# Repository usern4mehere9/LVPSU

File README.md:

# LVPSU
Low Voltage Power Supply Unit of Formula Student team "Black Hornets" from the University of Novi Sad Faculty of Technical Sciences

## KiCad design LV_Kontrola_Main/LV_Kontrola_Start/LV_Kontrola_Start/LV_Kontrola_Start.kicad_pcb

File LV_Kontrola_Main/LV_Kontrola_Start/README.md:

# LV\_Kontrola\_Start

Low Voltage Power Supply Unit of Formula Student team "Black Hornets" from the University of Novi Sad Faculty of Technical Sciences

LV\_Kontrola\_Start connectors:

START\_PWR:

1	\[GND]	GND\_START

2	\[GND]	GND\_START

3	\[GND]	GND\_START

4	\[GND]	GND\_START

5	\[VCC]	VCC\_START

6	\[VCC]	VCC\_START

7	\[VCC]	VCC\_START

8	\[VCC]	VCC\_START

COM:

1	\[GND]	GND\_START

2	\[COM]	RS485-B

3	\[GND]	GND\_START

4	\[COM]	RS485-A

START\_OUT\_A:

1	\[VCC]	5V4\_ISO\_1

2	\[GND]	GND\_ISO\_1

3	\[VCC]	5V4\_ISO\_2

4	\[GND]	GND\_ISO\_2

5	\[VCC]	5V4\_ISO\_3

6	\[GND]	GND\_ISO\_3

7	\[VCC]	5V4\_ISO\_4

8	\[GND]	GND\_ISO\_4

9	\[VCC]	3V7\_ISO\_1

10	\[GND]	GND\_ISO\_1

11	\[VCC]	3V7\_ISO\_2

12	\[GND]	GND\_ISO\_2

13	\[VCC]	3V7\_ISO\_3

14	\[GND]	GND\_ISO\_3

15	\[VCC]	3V7\_ISO\_4

16	\[GND]	GND\_ISO\_4

START\_OUT\_B:

1	\[VCC]	5V4\_ISO\_8

2	\[GND]	GND\_ISO\_8

3	\[VCC]	5V4\_ISO\_7

4	\[GND]	GND\_ISO\_7

5	\[VCC]	5V4\_ISO\_6

6	\[GND]	GND\_ISO\_6

7	\[VCC]	5V4\_ISO\_5

8	\[GND]	GND\_ISO\_5

9	\[VCC]	3V7\_ISO\_8

10	\[GND]	GND\_ISO\_8

11	\[VCC]	3V7\_ISO\_7

12	\[GND]	GND\_ISO\_7

13	\[VCC]	3V7\_ISO\_6

14	\[GND]	GND\_ISO\_6

15	\[VCC]	3V7\_ISO\_5

16	\[GND]	GND\_ISO\_5

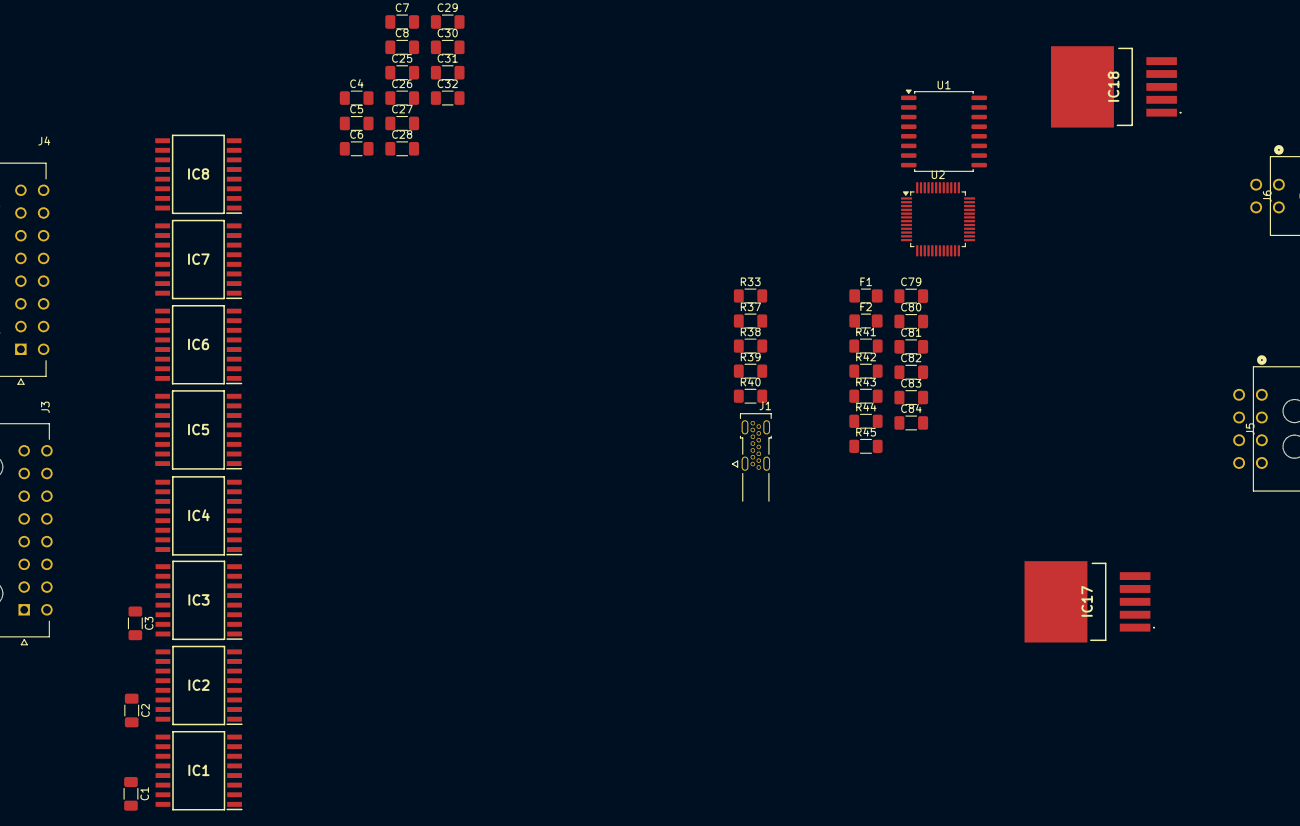
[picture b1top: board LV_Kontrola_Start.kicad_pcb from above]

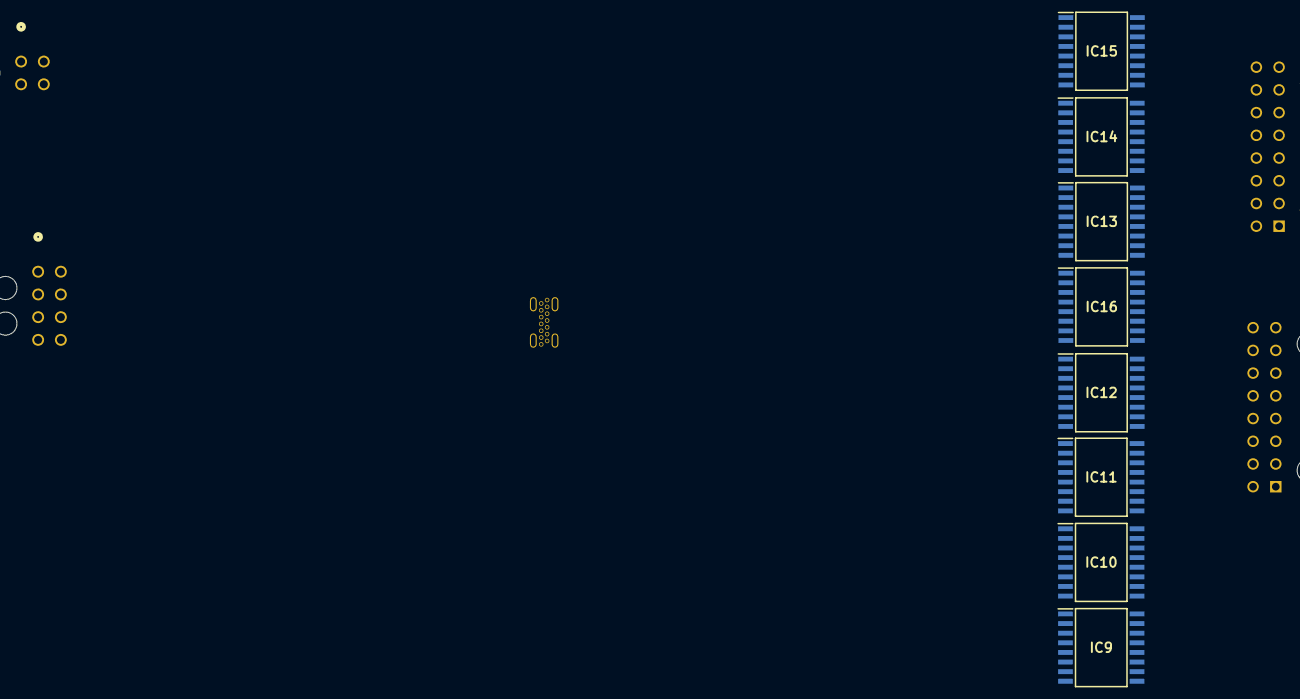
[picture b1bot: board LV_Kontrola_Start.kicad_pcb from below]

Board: 2 copper layers, 59 parts (8 on the bottom side), 44 nets, no tracks yet.

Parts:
C1, C2, C3, C4, C29, C30, C31, C32: 0.1uF; C_1206_3216Metric_Pad1.33x1.80mm_HandSolder
C5, C6, C7, C8, C25, C26, C27, C28, C81, C84: 10uF; C_1206_3216Metric_Pad1.33x1.80mm_HandSolder
C79, C82: 47uF; C_1206_3216Metric_Pad1.33x1.80mm_HandSolder
C80, C83: 22uF; C_1206_3216Metric_Pad1.33x1.80mm_HandSolder
F1, F2: 1A; Fuse_1206_3216Metric_Pad1.42x1.75mm_HandSolder
IC1, IC2, IC3, IC4, IC5, IC6, IC7, IC8, IC9, IC10, IC11, IC12, IC13, IC14, IC15, IC16: UCC12040DVE; SOIC127P1030X265-16N
IC17, IC18: MIC29152WU
J1: 2169890001; MOLEX_2169890001
J3, J4: 430451600; MOLEX_430451600
J5: 430450800; CONN_SD-43045-001_08_MOL
J6: 430450400; CONN_SD-43045-001_04_MOL
R33, R40: 5K1; R_1206_3216Metric_Pad1.30x1.75mm_HandSolder
R37, R38: 27R; R_1206_3216Metric_Pad1.30x1.75mm_HandSolder
R39: 1K5; R_1206_3216Metric_Pad1.30x1.75mm_HandSolder
R41: 34k; R_1206_3216Metric_Pad1.30x1.75mm_HandSolder
R42, R43: 10K; R_1206_3216Metric_Pad1.30x1.75mm_HandSolder
R44: 33k; R_1206_3216Metric_Pad1.30x1.75mm_HandSolder
R45: 10k; R_1206_3216Metric_Pad1.30x1.75mm_HandSolder
U1: ADM2483xRW; SOIC-16W_7.5x10.3mm_P1.27mm
U2: STM32F103C8Tx; LQFP-48_7x7mm_P0.5mm

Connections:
+3V7_ISO1: IC9.14 (VISO), J3.9
+3V7_ISO2: IC10.14 (VISO), J3.11
+3V7_ISO3: IC11.14 (VISO), J3.13
+3V7_ISO4: IC12.14 (VISO), J3.15
+3V7_ISO5: IC15.14 (VISO), J4.15
+3V7_ISO6: IC14.14 (VISO), J4.13
+3V7_ISO7: IC13.14 (VISO), J4.11
+3V7_ISO8: IC16.14 (VISO), J4.9
+5V4_ISO1: C1.1, C5.1, IC1.14 (VISO), J3.1
+5V4_ISO2: C2.1, C6.1, IC2.14 (VISO), J3.3
+5V4_ISO3: C3.1, C7.1, IC3.14 (VISO), J3.5
+5V4_ISO4: C4.1, C8.1, IC4.14 (VISO), J3.7
+5V4_ISO5: C28.1, C32.1, IC8.14 (VISO), J4.7
+5V4_ISO6: C27.1, C31.1, IC7.14 (VISO), J4.5
+5V4_ISO7: C26.1, C30.1, IC6.14 (VISO), J4.3
+5V4_ISO8: C25.1, C29.1, IC5.14 (VISO), J4.1
+5V_START: C82.2, F2.2, IC1.3 (VINP), IC2.3 (VINP), IC3.3 (VINP), IC4.3 (VINP), IC5.3 (VINP), IC6.3 (VINP), IC7.3 (VINP), IC8.3 (VINP), IC9.3 (VINP), IC10.3 (VINP), IC11.3 (VINP), IC12.3 (VINP), IC13.3 (VINP), IC14.3 (VINP), IC15.3 (VINP), IC16.3 (VINP), U1.16 (VDD2)
+V_START: C81.2, C84.2, IC17.2 (IN), IC18.2 (IN), J5.5, J5.6, J5.7, J5.8
CON_DN: J1.A7 (DA-), J1.B7 (DB-), R37.1
CON_DP: J1.A6 (DA+), J1.B6 (DB+), R38.2, R39.2
GND_ISO1: C1.2, C5.2, IC1.9 (GNDS_1), IC1.10 (NC_4), IC1.11 (NC_5), IC1.12 (NC_6), IC1.15 (GNDS_2), IC1.16 (GNDS_3), IC9.9 (GNDS_1), IC9.10 (NC_4), IC9.11 (NC_5), IC9.12 (NC_6), IC9.15 (GNDS_2), IC9.16 (GNDS_3), J3.2, J3.10
GND_ISO2: C2.2, C6.2, IC2.9 (GNDS_1), IC2.10 (NC_4), IC2.11 (NC_5), IC2.12 (NC_6), IC2.15 (GNDS_2), IC2.16 (GNDS_3), IC10.9 (GNDS_1), IC10.10 (NC_4), IC10.11 (NC_5), IC10.12 (NC_6), IC10.15 (GNDS_2), IC10.16 (GNDS_3), J3.4, J3.12
GND_ISO3: C3.2, C7.2, IC3.9 (GNDS_1), IC3.10 (NC_4), IC3.11 (NC_5), IC3.12 (NC_6), IC3.15 (GNDS_2), IC3.16 (GNDS_3), IC11.9 (GNDS_1), IC11.10 (NC_4), IC11.11 (NC_5), IC11.12 (NC_6), IC11.15 (GNDS_2), IC11.16 (GNDS_3), J3.6, J3.14
GND_ISO4: C4.2, C8.2, IC4.9 (GNDS_1), IC4.10 (NC_4), IC4.11 (NC_5), IC4.12 (NC_6), IC4.15 (GNDS_2), IC4.16 (GNDS_3), IC12.9 (GNDS_1), IC12.10 (NC_4), IC12.11 (NC_5), IC12.12 (NC_6), IC12.15 (GNDS_2), IC12.16 (GNDS_3), J3.8, J3.16
GND_ISO5: C28.2, C32.2, IC8.9 (GNDS_1), IC8.10 (NC_4), IC8.11 (NC_5), IC8.12 (NC_6), IC8.15 (GNDS_2), IC8.16 (GNDS_3), IC15.9 (GNDS_1), IC15.10 (NC_4), IC15.11 (NC_5), IC15.12 (NC_6), IC15.15 (GNDS_2), IC15.16 (GNDS_3), J4.8, J4.16
GND_ISO6: C27.2, C31.2, IC7.9 (GNDS_1), IC7.10 (NC_4), IC7.11 (NC_5), IC7.12 (NC_6), IC7.15 (GNDS_2), IC7.16 (GNDS_3), IC14.9 (GNDS_1), IC14.10 (NC_4), IC14.11 (NC_5), IC14.12 (NC_6), IC14.15 (GNDS_2), IC14.16 (GNDS_3), J4.6, J4.14
GND_ISO7: C26.2, C30.2, IC6.9 (GNDS_1), IC6.10 (NC_4), IC6.11 (NC_5), IC6.12 (NC_6), IC6.15 (GNDS_2), IC6.16 (GNDS_3), IC13.9 (GNDS_1), IC13.10 (NC_4), IC13.11 (NC_5), IC13.12 (NC_6), IC13.15 (GNDS_2), IC13.16 (GNDS_3), J4.4, J4.12
GND_ISO8: C25.2, C29.2, IC5.9 (GNDS_1), IC5.10 (NC_4), IC5.11 (NC_5), IC5.12 (NC_6), IC5.15 (GNDS_2), IC5.16 (GNDS_3), IC16.9 (GNDS_1), IC16.10 (NC_4), IC16.11 (NC_5), IC16.12 (NC_6), IC16.15 (GNDS_2), IC16.16 (GNDS_3), J4.2, J4.10
unnamed: IC17.5 (ADJ), R41.1, R42.2
unnamed: C80.2, F1.1, IC17.4 (OUT)
unnamed: IC18.5 (ADJ), R44.1, R45.2
unnamed: C83.2, F2.1, IC18.4 (OUT)
unnamed: J1.A5 (CC1), R33.1
unnamed: J1.B5 (CC2), R40.2
unnamed: R42.1, R43.2
RESET: C79.1, C80.1, C81.1, C82.1, C83.1, C84.1, IC1.2 (GNDP), IC1.4 (SYNC), IC1.6 (NC_1), IC1.7 (NC_2), IC1.8 (NC_3), IC2.2 (GNDP), IC2.4 (SYNC), IC2.6 (NC_1), IC2.7 (NC_2), IC2.8 (NC_3), IC3.2 (GNDP), IC3.4 (SYNC), IC3.6 (NC_1), IC3.7 (NC_2), IC3.8 (NC_3), IC4.2 (GNDP), IC4.4 (SYNC), IC4.6 (NC_1), IC4.7 (NC_2), IC4.8 (NC_3), IC5.2 (GNDP), IC5.4 (SYNC), IC5.6 (NC_1), IC5.7 (NC_2), IC5.8 (NC_3), IC6.2 (GNDP), IC6.4 (SYNC), IC6.6 (NC_1), IC6.7 (NC_2), IC6.8 (NC_3), IC7.2 (GNDP), IC7.4 (SYNC), IC7.6 (NC_1), IC7.7 (NC_2), IC7.8 (NC_3), IC8.2 (GNDP), IC8.4 (SYNC), IC8.6 (NC_1), IC8.7 (NC_2), IC8.8 (NC_3), IC9.2 (GNDP), IC9.4 (SYNC), IC9.6 (NC_1), IC9.7 (NC_2), IC9.8 (NC_3), IC10.2 (GNDP), IC10.4 (SYNC), IC10.6 (NC_1), IC10.7 (NC_2), IC10.8 (NC_3), IC11.2 (GNDP), IC11.4 (SYNC), IC11.6 (NC_1), IC11.7 (NC_2), IC11.8 (NC_3), IC12.2 (GNDP), IC12.4 (SYNC), IC12.6 (NC_1), IC12.7 (NC_2), IC12.8 (NC_3), IC13.2 (GNDP), IC13.4 (SYNC), IC13.6 (NC_1), IC13.7 (NC_2), IC13.8 (NC_3), IC14.2 (GNDP), IC14.4 (SYNC), IC14.6 (NC_1), IC14.7 (NC_2), IC14.8 (NC_3), IC15.2 (GNDP), IC15.4 (SYNC), IC15.6 (NC_1), IC15.7 (NC_2), IC15.8 (NC_3), IC16.2 (GNDP), IC16.4 (SYNC), IC16.6 (NC_1), IC16.7 (NC_2), IC16.8 (NC_3), IC17.3 (GND_1), IC17.6 (GND_2), IC18.3 (GND_1), IC18.6 (GND_2), J1.A1 (GND1), J1.A12 (GND2), J1.B1 (GND3), J1.B12 (GND4), J1.SH1 (SHIELD1), J1.SH2 (SHIELD2), J1.SH3 (SHIELD3), J1.SH4 (SHIELD4), J5.1, J5.2, J5.3, J5.4, J6.1, J6.3, R33.2, R40.1, R43.1, R45.1, U1.2 (GND1), U1.8 (GND1), U1.9 (GND2), U1.15 (GND2), U2.7 (NRST), U2.8 (VSSA), U2.23 (VSS), U2.35 (VSS), U2.47 (VSS)
RS485-A: J6.4, U1.12 (A)
RS485-B: J6.2, U1.13 (B)
RS485-DIR: U1.4 (~RE), U1.5 (DE), U2.2 (PC13)
RS485-RX: U1.3 (RxD), U2.43 (PB7)
RS485-TX: U1.6 (TxD), U2.42 (PB6)
USB_DM: R37.2, U2.32 (PA11)
USB_DP: R38.1, U2.33 (PA12)
VBAT: C79.2, F1.2, R39.1, U1.1 (VDD1), U1.7 (PV), U2.1 (VBAT), U2.9 (VDDA), U2.24 (VDD), U2.36 (VDD), U2.48 (VDD)

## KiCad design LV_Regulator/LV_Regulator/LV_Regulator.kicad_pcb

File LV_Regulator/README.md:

# LV\_Regulator

Low Voltage Power Supply Unit of Formula Student team "Black Hornets" from the University of Novi Sad Faculty of Technical Sciences

LV\_Regulator connectors:

PWR\_IN:

1	\[GND]	BAT-

2	\[GND]	BAT-

3	\[GND]	BAT-

4	\[GND]	BAT-

5	\[VCC]	BAT+

6	\[VCC]	BAT+

7	\[VCC]	BAT+

8	\[VCC]	BAT+

COM:

1	\[COM]	RS485-B

2	\[COM]	RS485-A

3	\[GND]	GND\_ISO

4	\[VCC]	+5V\_ISO

START:

1	\[GND]	GND

2	\[GND]	GND

3	\[VCC]	5V\_EXT

4	\[VCC]	3V3\_EXT

PWR\_OUT:

1	\[VCC]	VOUT

2	\[VCC]	VOUT

3	\[VCC]	VOUT

4	\[VCC]	VOUT

5	\[GND]	GND

6	\[GND]	GND

7	\[GND]	GND

8	\[GND]	GND

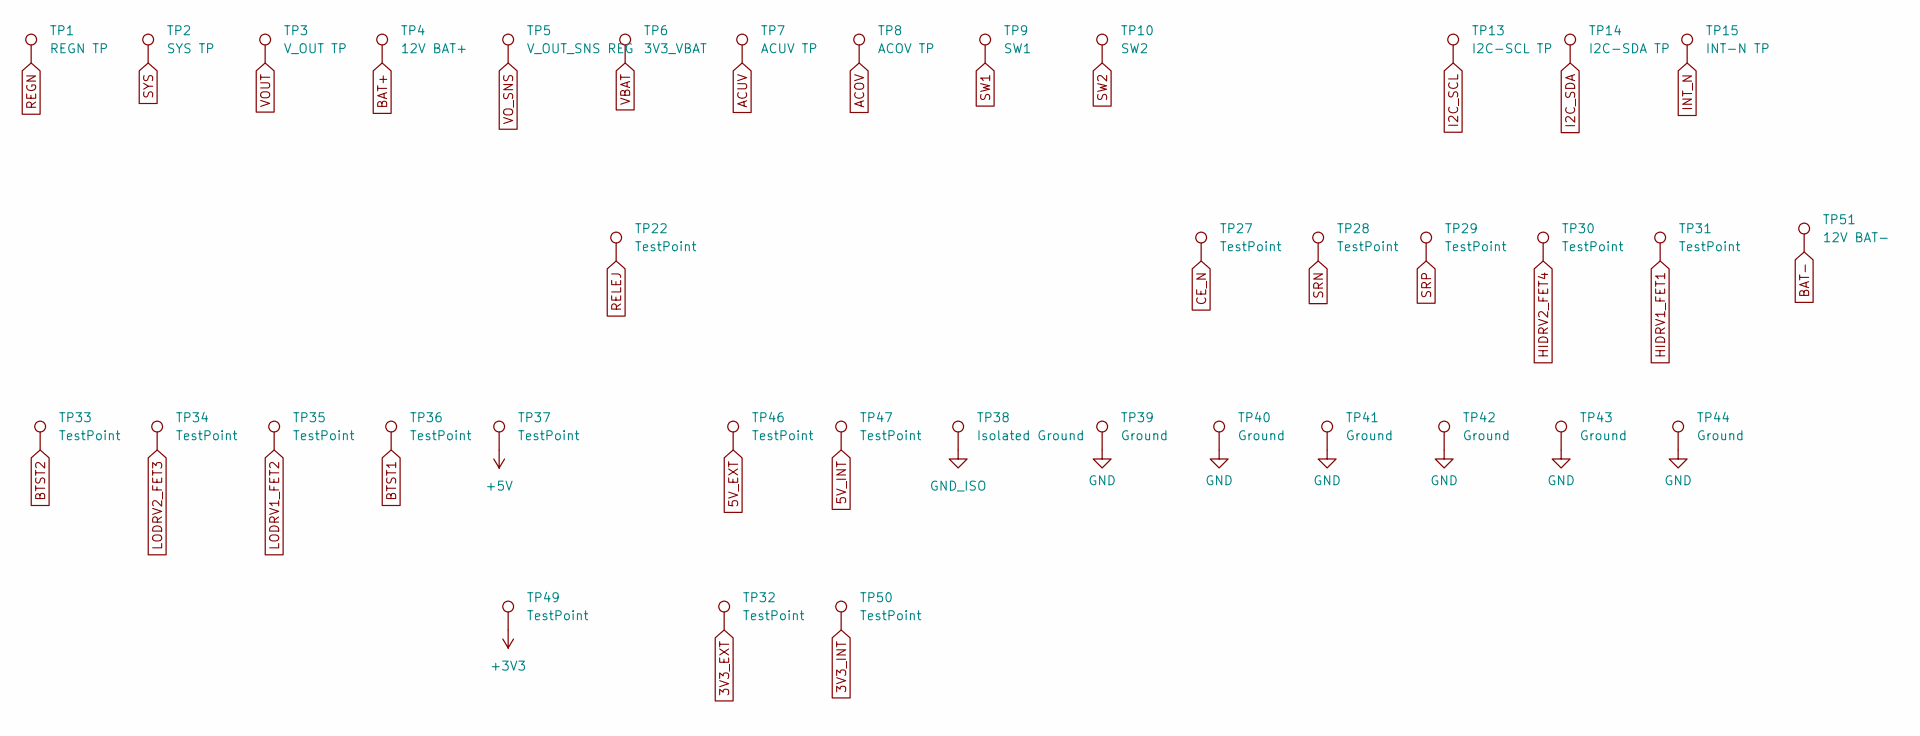
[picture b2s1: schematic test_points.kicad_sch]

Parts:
TP1: REGN TP; TestPoint_Pad_1.0x1.0mm
TP2: SYS TP; TestPoint_Pad_1.0x1.0mm
TP3: V_OUT TP; TestPoint_Pad_1.0x1.0mm
TP4: 12V BAT+; TestPoint_Pad_1.0x1.0mm
TP5: V_OUT_SNS REG; TestPoint_Pad_1.0x1.0mm
TP6: 3V3_VBAT; TestPoint_Pad_1.0x1.0mm
TP7: ACUV TP; TestPoint_Pad_1.0x1.0mm
TP8: ACOV TP; TestPoint_Pad_1.0x1.0mm
TP9: SW1; TestPoint_Pad_1.0x1.0mm
TP10: SW2; TestPoint_Pad_1.0x1.0mm
TP13: I2C-SCL TP; TestPoint_Pad_1.0x1.0mm
TP14: I2C-SDA TP; TestPoint_Pad_1.0x1.0mm
TP15: INT-N TP; TestPoint_Pad_1.0x1.0mm
TP22, TP27, TP28, TP29, TP30, TP31, TP32, TP33, TP34, TP35, TP36, TP37, TP46, TP47, TP49, TP50: TestPoint; TestPoint_Pad_1.0x1.0mm
TP38: Isolated Ground; TestPoint_Pad_1.0x1.0mm
TP39, TP40, TP41, TP42, TP43, TP44: Ground; TestPoint_Pad_1.0x1.0mm
TP51: 12V BAT-; TestPoint_Pad_1.0x1.0mm

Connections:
3V3_EXT: TP32.1 (1_1); also elsewhere on the board
3V3_INT: TP50.1 (1_1); also elsewhere on the board
5V_EXT: TP46.1 (1_1); also elsewhere on the board
5V_INT: TP47.1 (1_1); also elsewhere on the board
+5V: TP37.1 (1_1); also elsewhere on the board
ACOV: TP8.1 (1_1); also elsewhere on the board
ACUV: TP7.1 (1_1); also elsewhere on the board
BAT+: TP4.1 (1_1); also elsewhere on the board
BAT-: TP51.1 (1_1); also elsewhere on the board
BTST1: TP36.1 (1_1); also elsewhere on the board
BTST2: TP33.1 (1_1); also elsewhere on the board
CE_N: TP27.1 (1_1); also elsewhere on the board
GND: TP39.1 (1_1), TP40.1 (1_1), TP41.1 (1_1), TP42.1 (1_1), TP43.1 (1_1), TP44.1 (1_1); also elsewhere on the board
GND_ISO: TP38.1 (1_1); also elsewhere on the board
HIDRV1_FET1: TP31.1 (1_1); also elsewhere on the board
HIDRV2_FET4: TP30.1 (1_1); also elsewhere on the board
I2C_SCL: TP13.1 (1_1); also elsewhere on the board
I2C_SDA: TP14.1 (1_1); also elsewhere on the board
INT_N: TP15.1 (1_1); also elsewhere on the board
LODRV1_FET2: TP35.1 (1_1); also elsewhere on the board
LODRV2_FET3: TP34.1 (1_1); also elsewhere on the board
REGN: TP1.1 (1_1); also elsewhere on the board
RELEJ: TP22.1 (1_1); also elsewhere on the board
SRN: TP28.1 (1_1); also elsewhere on the board
SRP: TP29.1 (1_1); also elsewhere on the board
SW1: TP9.1 (1_1); also elsewhere on the board
SW2: TP10.1 (1_1); also elsewhere on the board
SYS: TP2.1 (1_1); also elsewhere on the board
VBAT: TP6.1 (1_1), TP49.1 (1_1); also elsewhere on the board
VOUT: TP3.1 (1_1), TP5.1 (1_1); also elsewhere on the board

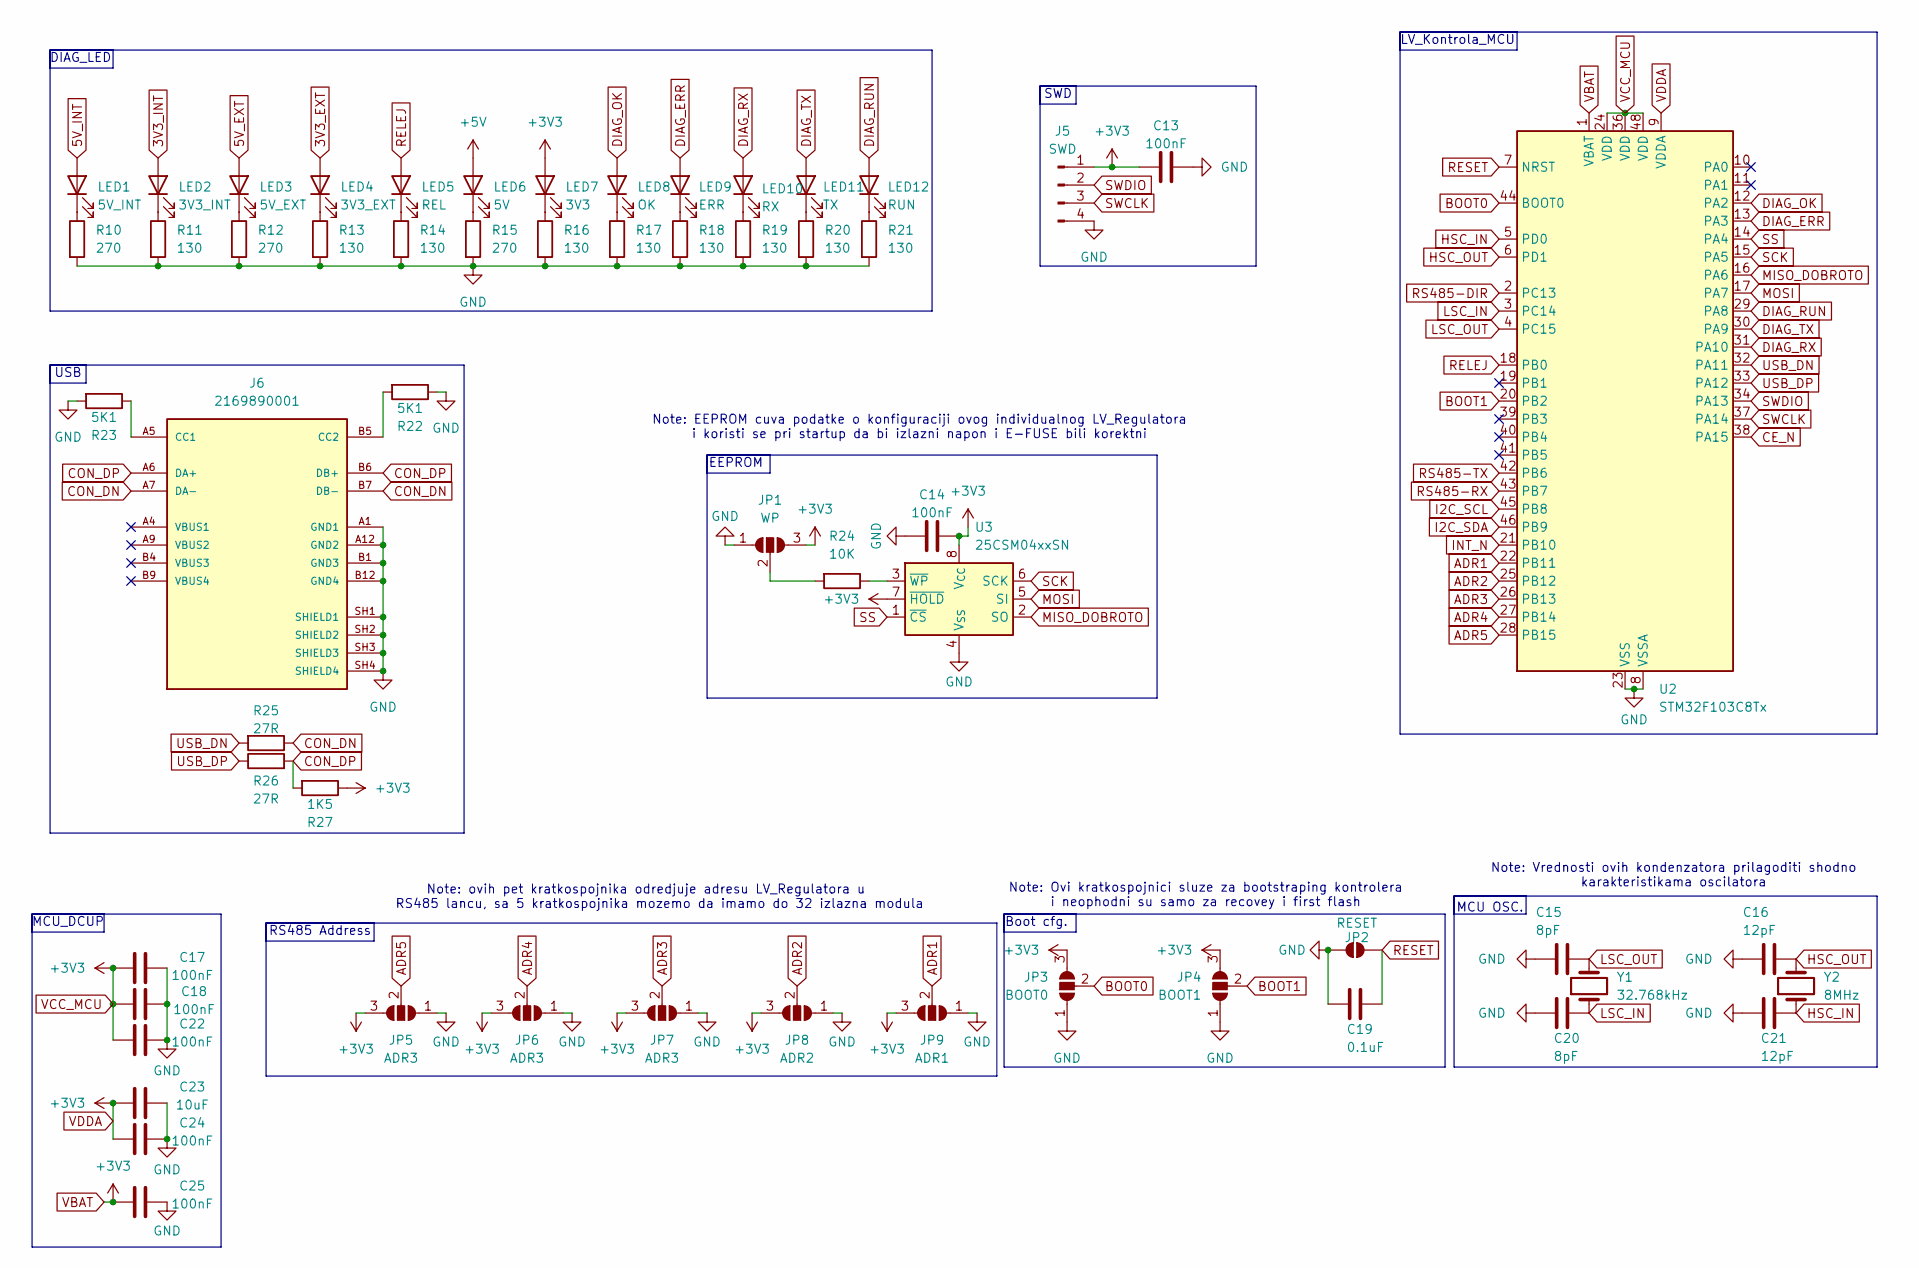
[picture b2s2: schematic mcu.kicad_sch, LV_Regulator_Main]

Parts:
C13, C14, C17, C18, C22, C24, C25: 100nF; C_1206_3216Metric_Pad1.33x1.80mm_HandSolder
C15, C20: 8pF; C_1206_3216Metric_Pad1.33x1.80mm_HandSolder
C16, C21: 12pF; C_1206_3216Metric_Pad1.33x1.80mm_HandSolder
C19: 0.1uF; C_1206_3216Metric_Pad1.33x1.80mm_HandSolder
C23: 10uF; C_1206_3216Metric_Pad1.33x1.80mm_HandSolder
J5: SWD; PinHeader_1x04_P2.54mm_Vertical
J6: 2169890001; MOLEX_2169890001; PARTREV B
JP1: WP; SolderJumper-3_P1.3mm_Open_RoundedPad1.0x1.5mm
JP2: RESET; SolderJumper-2_P1.3mm_Open_RoundedPad1.0x1.5mm
JP3: BOOT0; SolderJumper-3_P1.3mm_Open_RoundedPad1.0x1.5mm
JP4: BOOT1; SolderJumper-3_P1.3mm_Open_RoundedPad1.0x1.5mm
JP5, JP6, JP7: ADR3; SolderJumper-3_P1.3mm_Open_RoundedPad1.0x1.5mm
JP8: ADR2; SolderJumper-3_P1.3mm_Open_RoundedPad1.0x1.5mm
JP9: ADR1; SolderJumper-3_P1.3mm_Open_RoundedPad1.0x1.5mm
LED1: 5V_INT; LED_1206_3216Metric_Pad1.42x1.75mm_HandSolder
LED2: 3V3_INT; LED_1206_3216Metric_Pad1.42x1.75mm_HandSolder
LED3: 5V_EXT; LED_1206_3216Metric_Pad1.42x1.75mm_HandSolder
LED4: 3V3_EXT; LED_1206_3216Metric_Pad1.42x1.75mm_HandSolder
LED5: REL; LED_1206_3216Metric_Pad1.42x1.75mm_HandSolder
LED6: 5V; LED_1206_3216Metric_Pad1.42x1.75mm_HandSolder
LED7: 3V3; LED_1206_3216Metric_Pad1.42x1.75mm_HandSolder
LED8: OK; LED_1206_3216Metric_Pad1.42x1.75mm_HandSolder
LED9: ERR; LED_1206_3216Metric_Pad1.42x1.75mm_HandSolder
LED10: RX; LED_1206_3216Metric_Pad1.42x1.75mm_HandSolder
LED11: TX; LED_1206_3216Metric_Pad1.42x1.75mm_HandSolder
LED12: RUN; LED_1206_3216Metric_Pad1.42x1.75mm_HandSolder
R10, R12, R15: 270; R_1206_3216Metric_Pad1.30x1.75mm_HandSolder
R11, R13, R14, R16, R17, R18, R19, R20, R21: 130; R_1206_3216Metric_Pad1.30x1.75mm_HandSolder
R22, R23: 5K1; R_1206_3216Metric_Pad1.30x1.75mm_HandSolder
R24: 10K; R_1206_3216Metric_Pad1.30x1.75mm_HandSolder
R25, R26: 27R; R_1206_3216Metric_Pad1.30x1.75mm_HandSolder
R27: 1K5; R_1206_3216Metric_Pad1.30x1.75mm_HandSolder
U2: STM32F103C8Tx; LQFP-48_7x7mm_P0.5mm
U3: 25CSM04xxSN; SOIC-8_3.9x4.9mm_P1.27mm
Y1: 32.768kHz; Crystal_SMD_EuroQuartz_EQ161-2Pin_3.2x1.5mm_HandSoldering
Y2: 8MHz; Crystal_SMD_5032-2Pin_5.0x3.2mm_HandSoldering

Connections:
3V3_EXT: LED4.2 (A); also elsewhere on the board
3V3_INT: LED2.2 (A); also elsewhere on the board
5V_EXT: LED3.2 (A); also elsewhere on the board
5V_INT: LED1.2 (A); also elsewhere on the board
+5V: LED6.2 (A); also elsewhere on the board
ADR1: JP9.2 (C), U2.22 (PB11)
ADR2: JP8.2 (C), U2.25 (PB12)
ADR3: JP7.2 (C), U2.26 (PB13)
ADR4: JP6.2 (C), U2.27 (PB14)
ADR5: JP5.2 (C), U2.28 (PB15)
BOOT0: JP3.2 (C), U2.44 (BOOT0)
BOOT1: JP4.2 (C), U2.20 (PB2)
CE_N: U2.38 (PA15); also elsewhere on the board
CON_DN: J6.A7 (DA-), J6.B7 (DB-), R25.1
CON_DP: J6.A6 (DA+), J6.B6 (DB+), R26.2, R27.2
DIAG_ERR: LED9.2 (A), U2.13 (PA3)
DIAG_OK: LED8.2 (A), U2.12 (PA2)
DIAG_RUN: LED12.2 (A), U2.29 (PA8)
DIAG_RX: LED10.2 (A), U2.31 (PA10)
DIAG_TX: LED11.2 (A), U2.30 (PA9)
GND: C13.1, C14.2, C15.1, C16.1, C17.2, C18.2, C19.2, C20.2, C21.2, C22.2, C23.2, C24.2, C25.2, J5.4, J6.A1 (GND1), J6.A12 (GND2), J6.B1 (GND3), J6.B12 (GND4), J6.SH1 (SHIELD1), J6.SH2 (SHIELD2), J6.SH3 (SHIELD3), J6.SH4 (SHIELD4), JP1.1 (A), JP2.1 (A), JP3.1 (A), JP4.1 (A), JP5.1 (A), JP6.1 (A), JP7.1 (A), JP8.1 (A), JP9.1 (A), R10.2, R11.2, R12.2, R13.2, R14.2, R15.2, R16.2, R17.2, R18.2, R19.2, R20.2, R21.2, R22.1, R23.2, U2.8 (VSSA), U2.23 (VSS), U2.35 (VSS), U2.47 (VSS), U3.4 (V_{SS}); also elsewhere on the board
HSC_IN: C21.1, U2.5 (PD0), Y2.1
HSC_OUT: C16.2, U2.6 (PD1), Y2.2
I2C_SCL: U2.45 (PB8); also elsewhere on the board
I2C_SDA: U2.46 (PB9); also elsewhere on the board
INT_N: U2.21 (PB10); also elsewhere on the board
LSC_IN: C20.1, U2.3 (PC14), Y1.1
LSC_OUT: C15.2, U2.4 (PC15), Y1.2
MISO_DOBROTO: U2.16 (PA6), U3.2 (SO)
MOSI: U2.17 (PA7), U3.5 (SI)
unnamed: J6.A5 (CC1), R23.1
unnamed: J6.B5 (CC2), R22.2
unnamed: JP1.2 (C), R24.2
unnamed: LED1.1 (K), R10.1
unnamed: LED2.1 (K), R11.1
unnamed: LED3.1 (K), R12.1
unnamed: LED4.1 (K), R13.1
unnamed: LED5.1 (K), R14.1
unnamed: LED6.1 (K), R15.1
unnamed: LED7.1 (K), R16.1
unnamed: LED8.1 (K), R17.1
unnamed: LED9.1 (K), R18.1
unnamed: LED10.1 (K), R19.1
unnamed: LED11.1 (K), R20.1
unnamed: LED12.1 (K), R21.1
unnamed: R24.1, U3.3 (~WP)
RELEJ: LED5.2 (A), U2.18 (PB0); also elsewhere on the board
RESET: C19.1, JP2.2 (B), U2.7 (NRST)
RS485-DIR: U2.2 (PC13); also elsewhere on the board
RS485-RX: U2.43 (PB7); also elsewhere on the board
RS485-TX: U2.42 (PB6); also elsewhere on the board
SCK: U2.15 (PA5), U3.6 (SCK)
SS: U2.14 (PA4), U3.1 (~CS)
SWCLK: J5.3, U2.37 (PA14)
SWDIO: J5.2, U2.34 (PA13)
USB_DN: R25.2, U2.32 (PA11)
USB_DP: R26.1, U2.33 (PA12)
VBAT: C13.2, C14.1, C17.1, C18.1, C22.1, C23.1, C24.1, C25.1, J5.1, JP1.3 (B), JP3.3 (B), JP4.3 (B), JP5.3 (B), JP6.3 (B), JP7.3 (B), JP8.3 (B), JP9.3 (B), LED7.2 (A), R27.1, U2.1 (VBAT), U2.9 (VDDA), U2.24 (VDD), U2.36 (VDD), U2.48 (VDD), U3.7 (~HOLD), U3.8 (V_{CC}); also elsewhere on the board

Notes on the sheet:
RS485 Address
MCU_DCUP
EEPROM
LV_Kontrola_MCU
Note: Ovi kratkospojnici sluze za bootstraping kontrolera i neophodni su samo za recovey i first flash
USB
Boot cfg.
Note: Vrednosti ovih kondenzatora prilagoditi shodno karakteristikama oscilatora
Note: ovih pet kratkospojnika odredjuje adresu LV_Regulatora u RS485 lancu, sa 5 kratkospojnika mozemo da imamo do 32 izlazna modula
Note: EEPROM cuva podatke o konfiguraciji ovog individualnog LV_Regulatora i koristi se pri startup da bi izlazni napon i E-FUSE bili korektni
MCU OSC.
SWD
DIAG_LED

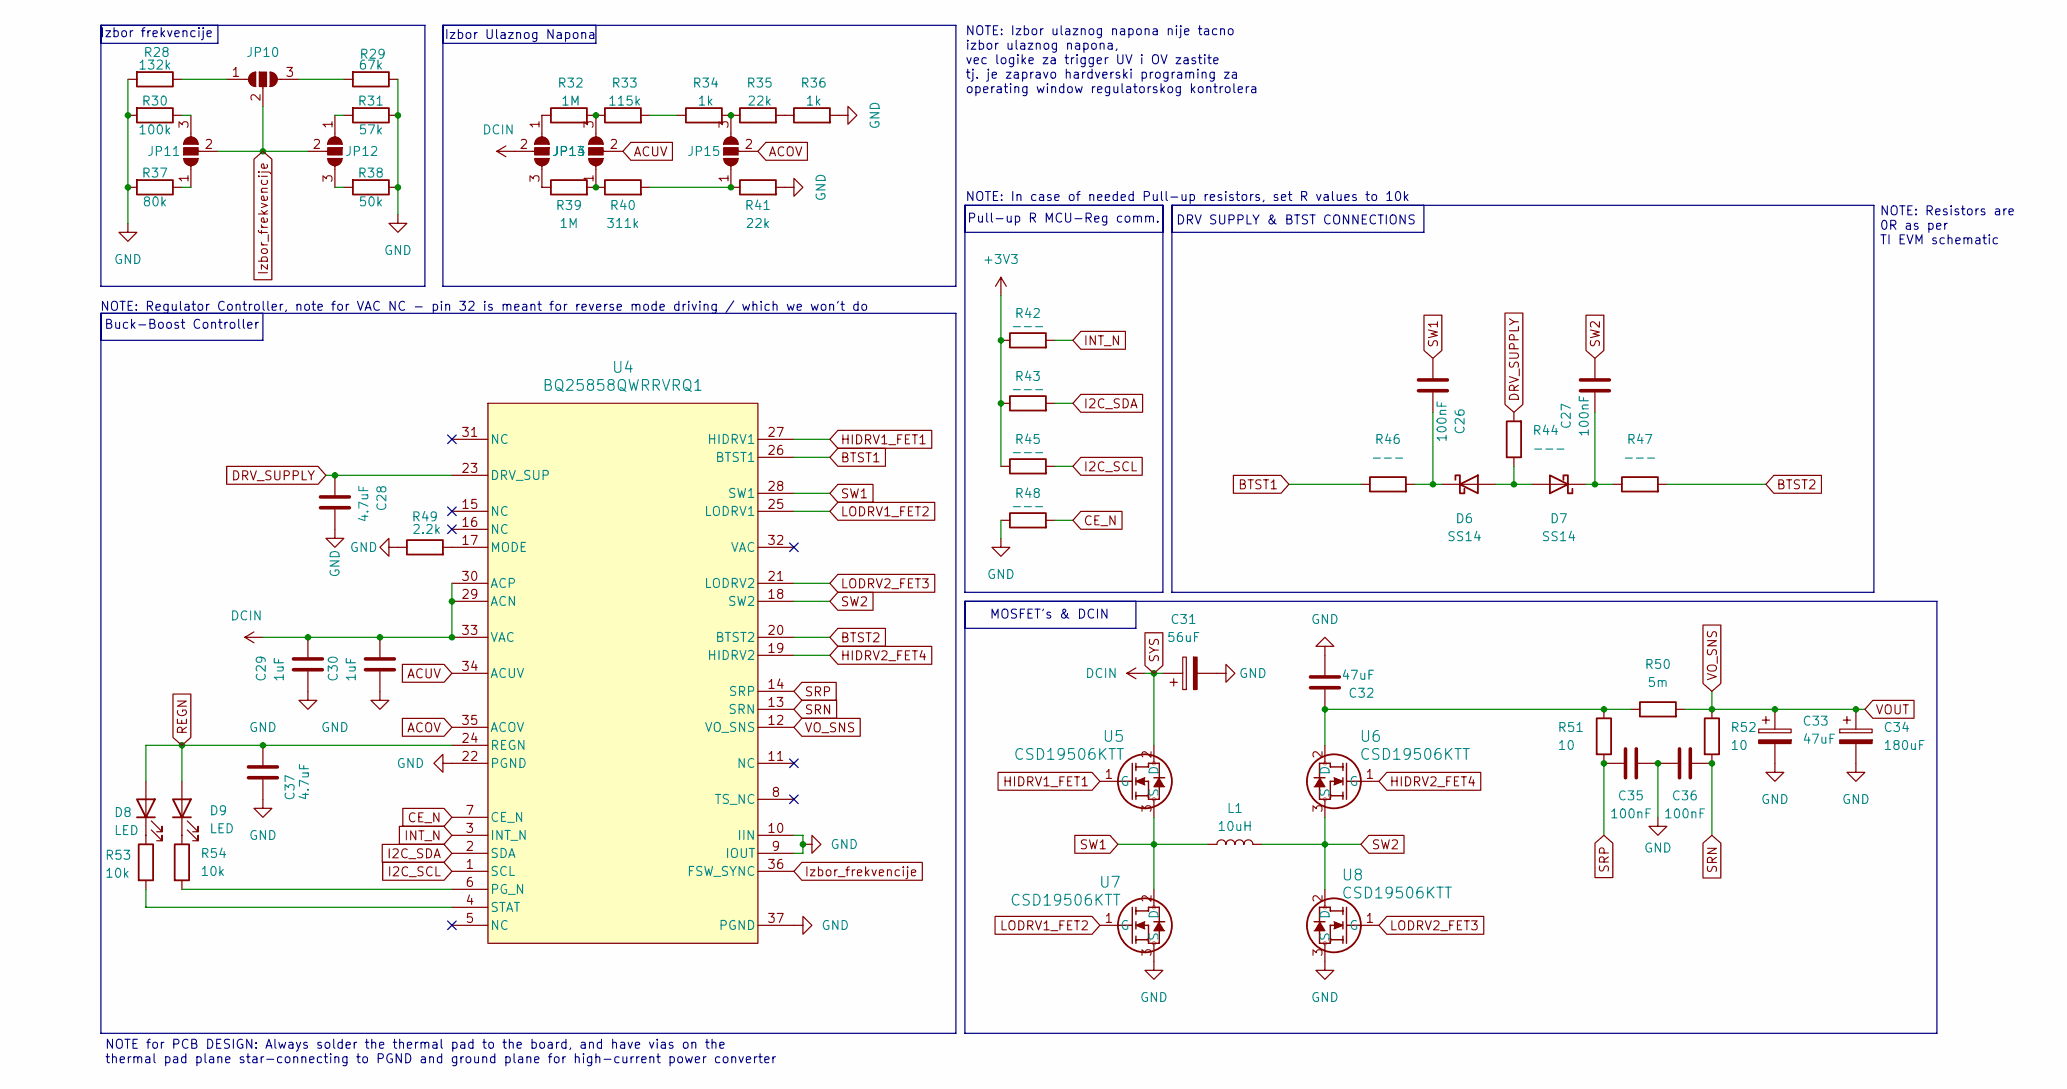
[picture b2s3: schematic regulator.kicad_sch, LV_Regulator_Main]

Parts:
C26, C27, C35, C36: 100nF; C_1206_3216Metric
C28, C37: 4.7uF; C_1206_3216Metric
C29, C30: 1uF; C_1206_3216Metric
C31: 56uF; CP_Elec_10x10
C32, C33: 47uF; CP_Elec_10x10
C34: 180uF; CAP_UCD_12P5X13P5_NCH
D6, D7: SS14; CR_SMA_403AE_OSI
D8, D9: LED; D_1206_3216Metric_Pad1.42x1.75mm_HandSolder
JP10, JP11, JP12, JP13, JP14, JP15: SolderJumper_3_Open; SolderJumper-3_P1.3mm_Open_RoundedPad1.0x1.5mm
L1: 10uH; L_APV_APH1770
R28: 132k; R_1206_3216Metric_Pad1.30x1.75mm_HandSolder
R29: 67k; R_1206_3216Metric_Pad1.30x1.75mm_HandSolder
R30: 100k; R_1206_3216Metric_Pad1.30x1.75mm_HandSolder
R31: 57k; R_1206_3216Metric_Pad1.30x1.75mm_HandSolder
R32, R39: 1M; R_1206_3216Metric_Pad1.30x1.75mm_HandSolder
R33: 115k; R_1206_3216Metric_Pad1.30x1.75mm_HandSolder
R34, R36: 1k; R_1206_3216Metric_Pad1.30x1.75mm_HandSolder
R35, R41: 22k; R_1206_3216Metric_Pad1.30x1.75mm_HandSolder
R37: 80k; R_1206_3216Metric_Pad1.30x1.75mm_HandSolder
R38: 50k; R_1206_3216Metric_Pad1.30x1.75mm_HandSolder
R40: 311k; R_1206_3216Metric_Pad1.30x1.75mm_HandSolder
R42, R43, R44, R45, R46, R47, R48: ---; R_1206_3216Metric_Pad1.30x1.75mm_HandSolder
R49: 2.2k; R_1206_3216Metric_Pad1.30x1.75mm_HandSolder
R50: 5m; RESC50110X70N
R51, R52: 10; R_1206_3216Metric_Pad1.30x1.75mm_HandSolder
R53, R54: 10k; R_1206_3216Metric_Pad1.30x1.75mm_HandSolder
U4: BQ25858QWRRVRQ1; RRV0036B-IPC_A
U5, U6, U7, U8: CSD19506KTT; DDPAK&slash_TO-263_KTT_TEX

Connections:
ACOV: JP15.2 (C), U4.35 (ACOV); also elsewhere on the board
ACUV: JP14.2 (C), U4.34 (ACUV); also elsewhere on the board
BTST1: R46.1, U4.26 (BTST1); also elsewhere on the board
BTST2: R47.2, U4.20 (BTST2); also elsewhere on the board
CE_N: R48.2, U4.7 (CE_N); also elsewhere on the board
DRV_SUPPLY: C28.1, R44.2, U4.23 (DRV_SUP)
GND: C28.2, C29.1, C30.1, C31.2, C32.2, C33.2, C34.2, C35.2, C36.1, C37.1, R28.2, R29.1, R30.2, R31.1, R36.2, R37.2, R38.1, R41.2, R48.1, R49.1, U4.9 (IOUT), U4.10 (IIN), U4.22 (PGND), U4.37 (PGND), U7.3 (S), U8.3 (S); also elsewhere on the board
HIDRV1_FET1: U4.27 (HIDRV1), U5.1 (G); also elsewhere on the board
HIDRV2_FET4: U4.19 (HIDRV2), U6.1 (G); also elsewhere on the board
I2C_SCL: R45.2, U4.1 (SCL); also elsewhere on the board
I2C_SDA: R43.2, U4.2 (SDA); also elsewhere on the board
INT_N: R42.2, U4.3 (INT_N); also elsewhere on the board
Izbor_frekvencije: JP10.2 (C), JP11.2 (C), JP12.2 (C), U4.36 (FSW_SYNC)
LODRV1_FET2: U4.25 (LODRV1), U7.1 (G); also elsewhere on the board
LODRV2_FET3: U4.21 (LODRV2), U8.1 (G); also elsewhere on the board
unnamed: D6.2 (A), D7.2 (A), R44.1
unnamed: C26.2, D6.1 (K), R46.2
unnamed: C27.2, D7.1 (K), R47.1
unnamed: D8.1 (K), R53.1
unnamed: D9.1 (K), R54.1
unnamed: JP10.1 (A), R28.1
unnamed: JP10.3 (B), R29.2
unnamed: JP11.1 (A), R37.1
unnamed: JP11.3 (B), R30.1
unnamed: JP12.1 (A), R31.2
unnamed: JP12.3 (B), R38.2
unnamed: JP13.1 (A), R32.1
unnamed: JP13.3 (B), R39.1
unnamed: JP14.1 (A), R39.2, R40.1
unnamed: JP14.3 (B), R32.2, R33.1
unnamed: JP15.1 (A), R40.2, R41.1
unnamed: JP15.3 (B), R34.2, R35.1
unnamed: R33.2, R34.1
unnamed: R35.2, R36.1
unnamed: R49.2, U4.17 (MODE)
unnamed: R54.2, U4.6 (PG_N)
unnamed: R53.2, U4.4 (STAT)
unnamed: C32.1, R50.1, R51.1, U6.2 (D)
REGN: C37.2, D8.2 (A), D9.2 (A), U4.24 (REGN); also elsewhere on the board
SRN: C36.2, R52.2, U4.13 (SRN); also elsewhere on the board
SRP: C35.1, R51.2, U4.14 (SRP); also elsewhere on the board
SW1: C26.1, L1.1, U4.28 (SW1), U5.3 (S), U7.2 (D); also elsewhere on the board
SW2: C27.1, L1.2, U4.18 (SW2), U6.3 (S), U8.2 (D); also elsewhere on the board
SYS: C29.2, C30.2, C31.1, JP13.2 (C), U4.29 (ACN), U4.30 (ACP), U4.33 (VAC), U5.2 (D); also elsewhere on the board
VBAT: R42.1, R43.1, R45.1; also elsewhere on the board
VOUT: C33.1, C34.1, R50.2, R52.1, U4.12 (VO_SNS); also elsewhere on the board

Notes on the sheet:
Buck-Boost Controller
NOTE: Resistors are 0R as per TI EVM schematic
MOSFET's & DCIN
Pull-up R MCU-Reg comm.
Izbor Ulaznog Napona
NOTE: In case of needed Pull-up resistors, set R values to 10k
DRV SUPPLY & BTST CONNECTIONS
NOTE: Izbor ulaznog napona nije tacno izbor ulaznog napona, vec logike za trigger UV i OV zastite tj. je zapravo hardverski programing za operating window regulatorskog kontrolera
Izbor frekvencije
NOTE: Regulator Controller, note for VAC NC - pin 32 is meant for reverse mode driving / which we won't do
NOTE for PCB DESIGN: Always solder the thermal pad to the board, and have vias on the thermal pad plane star-connecting to PGND and ground plane for high-current power converter
